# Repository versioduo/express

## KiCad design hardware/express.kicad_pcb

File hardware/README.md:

# express
🎚️ MIDI Expression Controller

## Schematic
[PDF](express.pdf)

## Bill Of Materials
[Interactive BOM](https://html-preview.github.io/?url=https://github.com/versioduo/express/main/hardware/express-bom.html)

# Copying
Anyone can use this public domain work without having to seek authorisation, no one can ever own it.

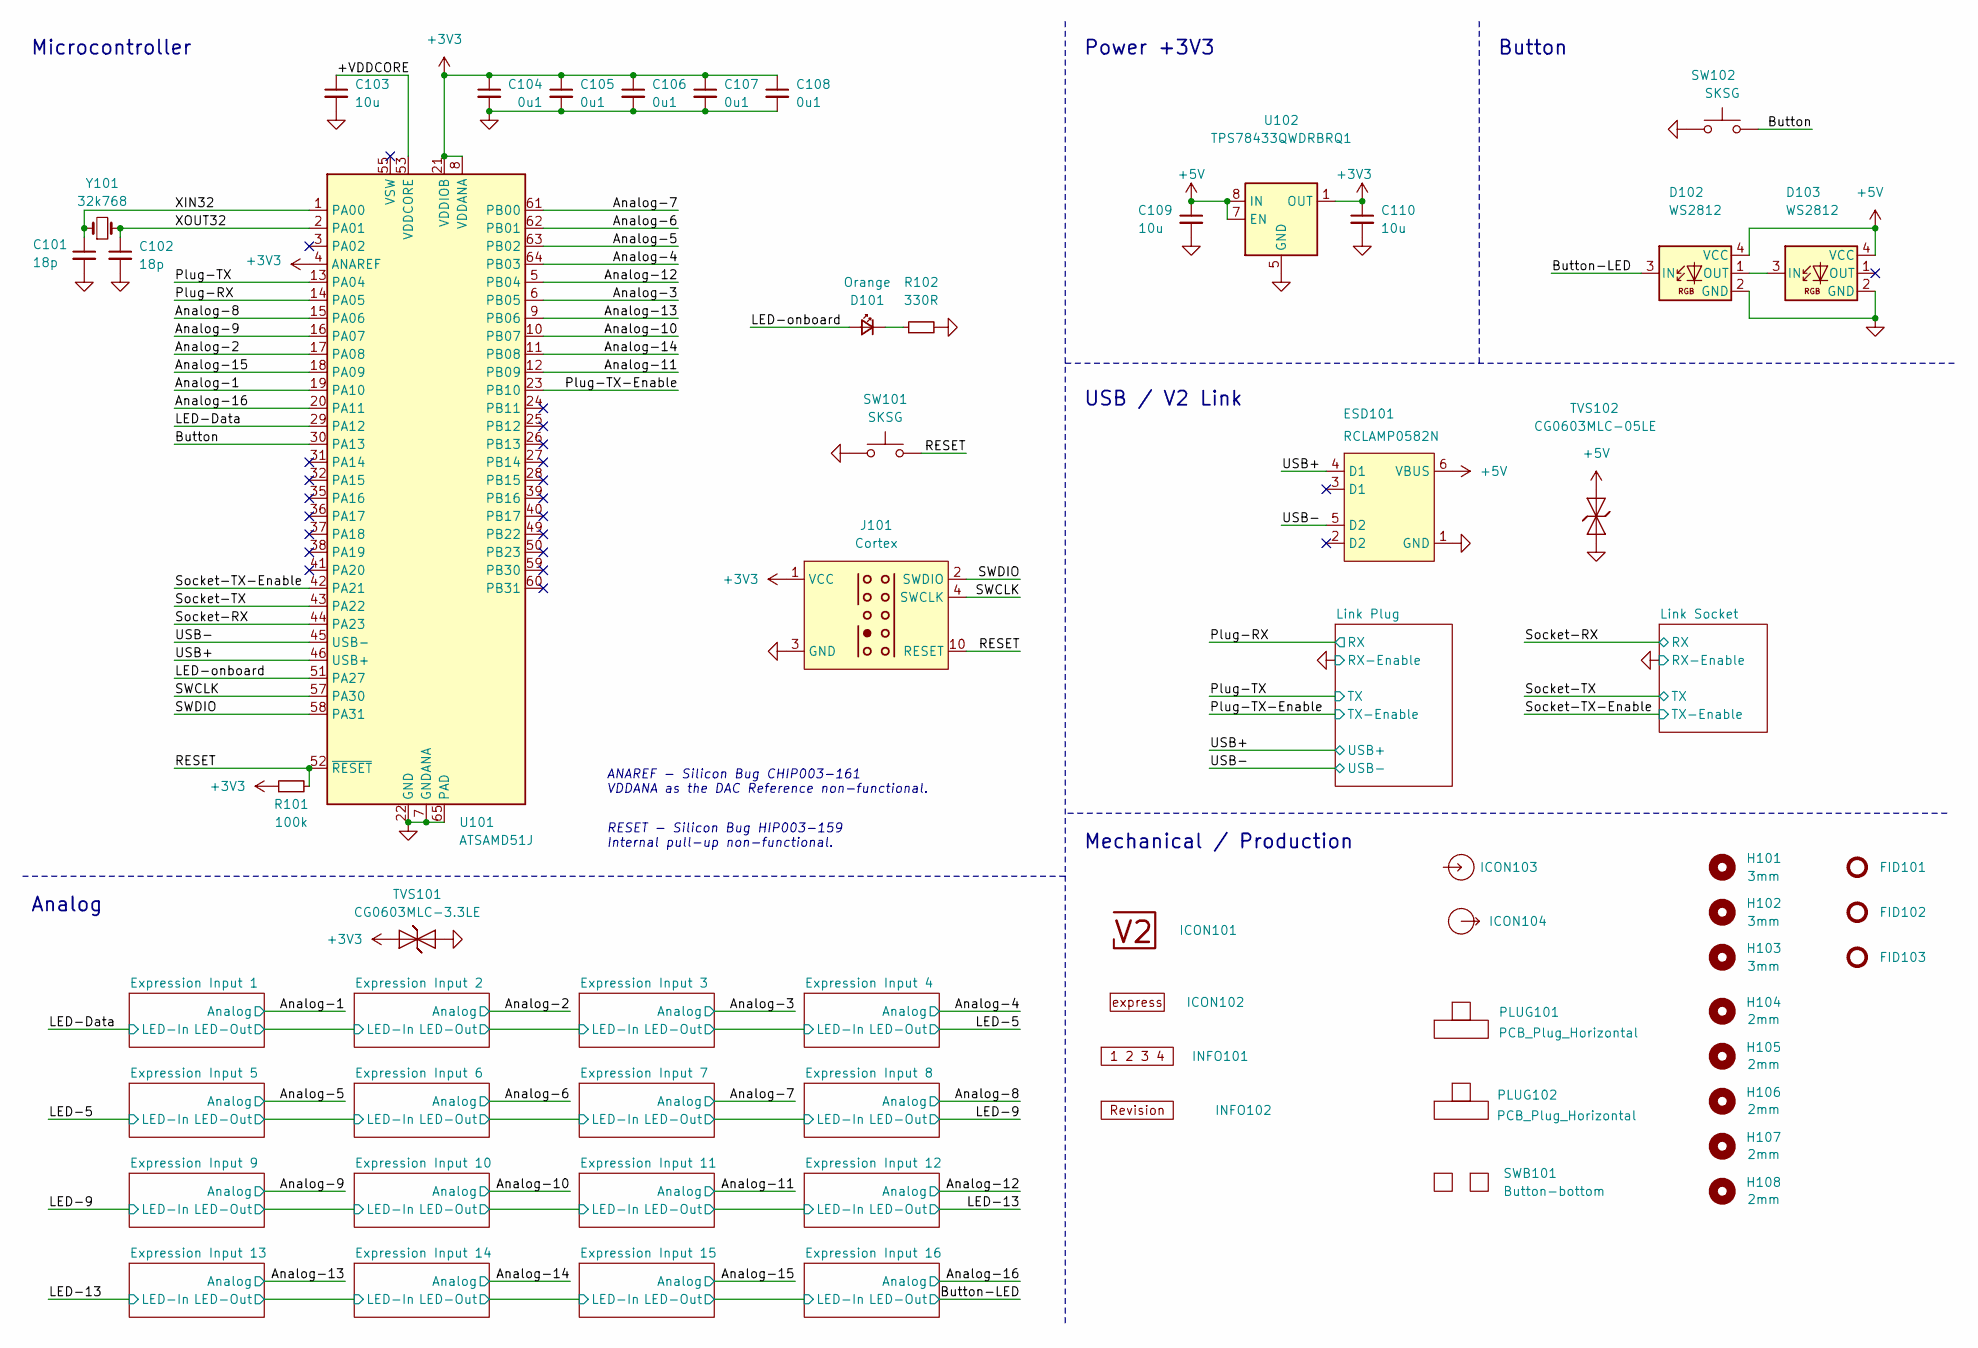
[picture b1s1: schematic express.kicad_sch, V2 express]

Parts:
C101, C102: 18p; C_0603; Rating 50V; Mouser 810-CGA3E2C0G1H180J
C103: 10u; C_0603; Rating 10V; Mouser 810-C1608X6S1A106M
C104, C105, C106, C107, C108: 0u1; C_0603; Rating 50V; Mouser 810-CGA3E2X7R1H104MA
C109, C110: 10u; C_0805; Rating 25V; Mouser 810-C2012X5R1E106K
D101: Orange; LED_0603; Rating 605nm; Mouser 755-SML-D12D1WT86
D102, D103: WS2812; WS2812-2020; Rating 15mA; LCSC C965555
ESD101: RCLAMP0582N; SLP1210N6; Rating 20kV; Mouser 947-RCLAMP0582N.TCT
FID101, FID102, FID103: Fiducial_Paste; Fiducial_0.5mm_Mask1mm_Paste
H101, H102, H103: 3mm; MountingHole_3mm
H104, H105, H106, H107, H108: 2mm; MountingHole_2mm
ICON101: V2-logo; Logo_Small
ICON102: Board_express; Board_express_Small
ICON103: Arrow_In
ICON104: Arrow_Out
INFO101: Layer_Numbers
INFO102: Revision
J101: Cortex
PLUG101, PLUG102: PCB_Plug_Horizontal
R101: 100k; R_0603; Rating 100mW; Mouser 71-CRCW0603100KFKEAC
R102: 330R; R_0603; Rating 100mW; Mouser 71-CRCW0603330RFKEAC
SW101, SW102: SKSG; Rating 1.6N; Mouser 688-SKSGACE010
SWB101: Button-bottom; PCB_Button-bottom
TVS101: CG0603MLC-3.3LE; D_0603; Rating 3V3; Mouser 652-CG0603MLC-3.3LE
TVS102: CG0603MLC-05LE; D_0603; Rating 5V; Mouser 652-CG0603MLC-05LE
U101: ATSAMD51J; QFN-64-1EP_9x9mm_P0.5mm_EP4.8x4.8mm_ThermalVias; Rating Cortex-M4F; Mouser 556-ATSAMD51J19AMU
U102: TPS78433QWDRBRQ1; VSON-8-1_3x3mm_P0.65_EP1.65x2.4mm; Rating 300mA; Mouser 595-TPS78433QWDRBRQ1
Y101: 32k768; Crystal_SMD_3215-2Pin_3.2x1.5mm; Rating 10ppm; Mouser 815-ABS0716632.768KT

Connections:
+3V3: C104.1, C105.1, C106.1, C107.1, C108.1, C110.1, J101.1 (VCC), R101.1, TVS101.1 (K), U101.4 (ANAREF), U101.8 (VDDANA), U101.21 (VDDIOB), U101.34 (VDDIO), U101.48 (VDDIO), U101.56 (VDDIO), U102.1 (OUT); also elsewhere on the board
+5V: C109.1, D102.4 (VCC), D103.4 (VCC), ESD101.6 (VBUS), TVS102.2 (A), U102.7 (EN), U102.8 (IN); also elsewhere on the board
/+VDDCORE: C103.1, U101.53 (VDDCORE)
/Analog-1: U101.19 (PA10); also elsewhere on the board
/Analog-2: U101.17 (PA08); also elsewhere on the board
/Analog-3: U101.6 (PB05); also elsewhere on the board
/Analog-4: U101.64 (PB03); also elsewhere on the board
/Analog-5: U101.63 (PB02); also elsewhere on the board
/Analog-6: U101.62 (PB01); also elsewhere on the board
/Analog-7: U101.61 (PB00); also elsewhere on the board
/Analog-8: U101.15 (PA06); also elsewhere on the board
/Analog-9: U101.16 (PA07); also elsewhere on the board
/Analog-10: U101.10 (PB07); also elsewhere on the board
/Analog-11: U101.12 (PB09); also elsewhere on the board
/Analog-12: U101.5 (PB04); also elsewhere on the board
/Analog-13: U101.9 (PB06); also elsewhere on the board
/Analog-14: U101.11 (PB08); also elsewhere on the board
/Analog-15: U101.18 (PA09); also elsewhere on the board
/Analog-16: U101.20 (PA11); also elsewhere on the board
/Button: SW102.2, U101.30 (PA13)
/Button-LED: D102.3 (IN); also elsewhere on the board
/LED-Data: U101.29 (PA12); also elsewhere on the board
/LED-onboard: D101.2 (A), U101.51 (PA27)
/Plug-RX: U101.14 (PA05); also elsewhere on the board
/Plug-TX: U101.13 (PA04); also elsewhere on the board
/Plug-TX-Enable: U101.23 (PB10); also elsewhere on the board
/RESET: J101.10 (RESET), R101.2, SW101.2, U101.52 (~RESET)
/SWCLK: J101.4 (SWCLK), U101.57 (PA30)
/SWDIO: J101.2 (SWDIO), U101.58 (PA31)
/Socket-RX: U101.44 (PA23); also elsewhere on the board
/Socket-TX: U101.43 (PA22); also elsewhere on the board
/Socket-TX-Enable: U101.42 (PA21); also elsewhere on the board
/USB+: ESD101.4 (D1), U101.46 (USB+); also elsewhere on the board
/USB-: ESD101.5 (D2), U101.45 (USB-); also elsewhere on the board
/XIN32: C101.1, U101.1 (PA00), Y101.1
/XOUT32: C102.1, U101.2 (PA01), Y101.2
GND: C101.2, C102.2, C103.2, C104.2, C105.2, C106.2, C107.2, C108.2, C109.2, C110.2, D102.2 (GND), D103.2 (GND), ESD101.1 (GND), J101.3 (GND), J101.5 (GND), R102.2, SW101.1, SW102.1, TVS101.2 (A), TVS102.1 (K), U101.7 (GNDANA), U101.22 (GND), U101.33 (GND), U101.47 (GND), U101.54 (GND), U101.65 (PAD), U102.5 (GND), U102.9 (GND); also elsewhere on the board
unnamed: D101.1 (K), R102.1
unnamed: D102.1 (OUT), D103.3 (IN)

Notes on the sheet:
ANAREF - ﻿Silicon Bug CHIP003-161 VDDANA as the DAC Reference non-functional.
Analog
RESET - ﻿Silicon Bug HIP003-159 Internal pull-up non-functional.
Button
Power +3V3
Mechanical / Production
Microcontroller
USB / V2 Link

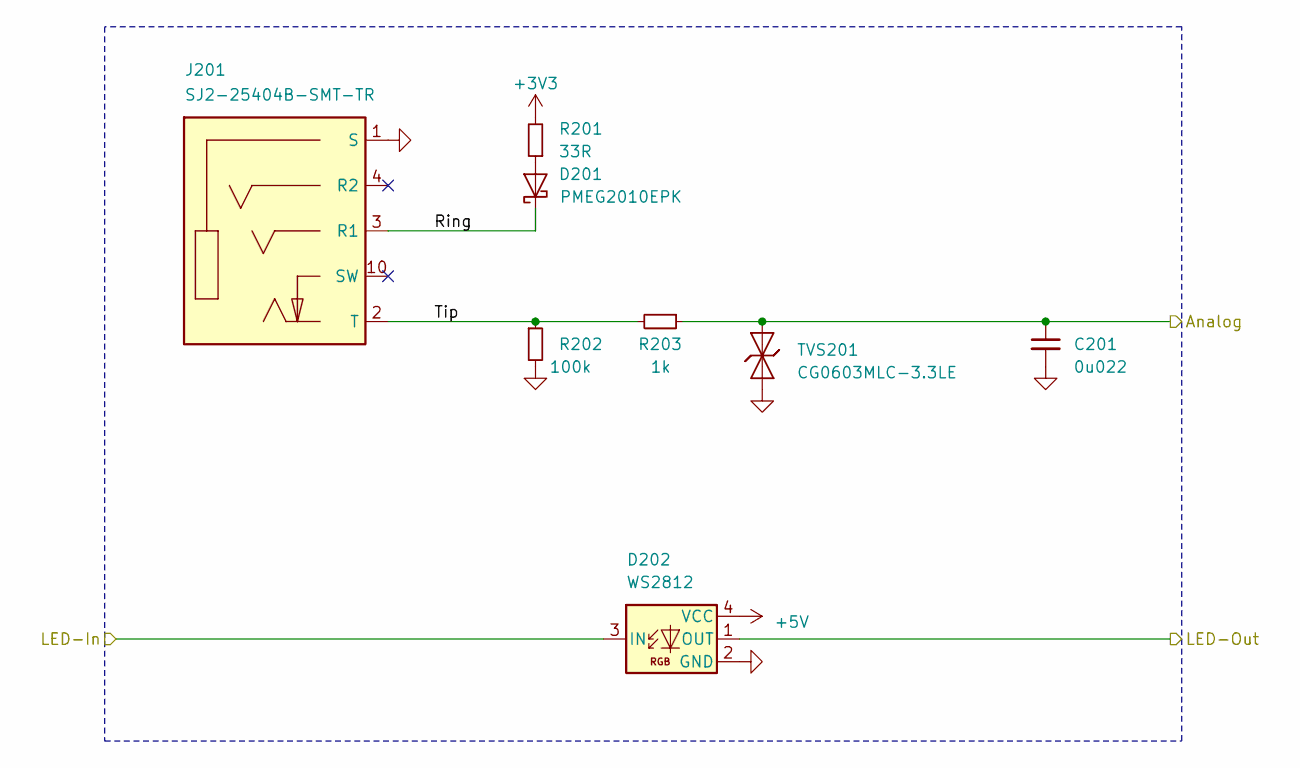
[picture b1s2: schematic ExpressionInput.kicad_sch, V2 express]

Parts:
C201: 0u022; C_0603; Rating 50V; Mouser 603-CC603KPX7R9BB223
D201: PMEG2010EPK; D_SOD-1608; Rating 20V; Mouser 771-PMEG2010EPK
D202: WS2812; WS2812-2020; Rating 15mA; LCSC C965555
J201: SJ2-25404B-SMT-TR; CUI_SJ2-25404B-SMT-TR; Rating 2.5mm; Mouser 490-SJ2-25404BSMT-TR
R201: 33R; R_0603; Rating 330mW; Mouser 71-CRCW060333R0FKEAH
R202: 100k; R_0603; Rating 100mW; Mouser 71-CRCW0603100KFKEAC
R203: 1k; R_0603; Rating 330mW; Mouser 71-CRCW06031K00FKEAH
TVS201: CG0603MLC-3.3LE; D_0603; Rating 3V3; Mouser 652-CG0603MLC-3.3LE

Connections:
+3V3: R201.2; also elsewhere on the board
+5V: D202.4 (VCC); also elsewhere on the board
/Analog-1: C201.1, R203.1, TVS201.2 (A); also elsewhere on the board
/Expression Input 1/LED-Out: D202.1 (OUT); also elsewhere on the board
/Expression Input 1/Ring: D201.1 (K), J201.3 (R1)
/Expression Input 1/Tip: J201.2 (T), R202.1, R203.2
/LED-Data: D202.3 (IN); also elsewhere on the board
GND: C201.2, D202.2 (GND), J201.1 (S), R202.2, TVS201.1 (K); also elsewhere on the board
unnamed: D201.2 (A), R201.1

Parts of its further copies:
C301, C401, C501, C601, C701, C801, C901, C1001, C1101, C1201, C1301, C1401, C1501, C1601, C1701: 0u022; C_0603; Rating 50V; Mouser 603-CC603KPX7R9BB223
D301, D401, D501, D601, D701, D801, D901, D1001, D1101, D1201, D1301, D1401, D1501, D1601, D1701: PMEG2010EPK; D_SOD-1608; Rating 20V; Mouser 771-PMEG2010EPK
D302, D402, D502, D602, D702, D802, D902, D1002, D1102, D1202, D1302, D1402, D1502, D1602, D1702: WS2812; WS2812-2020; Rating 15mA; LCSC C965555
J301, J401, J501, J601, J701, J801, J901, J1001, J1101, J1201, J1301, J1401, J1501, J1601, J1701: SJ2-25404B-SMT-TR; CUI_SJ2-25404B-SMT-TR; Rating 2.5mm; Mouser 490-SJ2-25404BSMT-TR
R301, R401, R501, R601, R701, R801, R901, R1001, R1101, R1201, R1301, R1401, R1501, R1601, R1701: 33R; R_0603; Rating 330mW; Mouser 71-CRCW060333R0FKEAH
R302, R402, R502, R602, R702, R802, R902, R1002, R1102, R1202, R1302, R1402, R1502, R1602, R1702: 100k; R_0603; Rating 100mW; Mouser 71-CRCW0603100KFKEAC
R303, R403, R503, R603, R703, R803, R903, R1003, R1103, R1203, R1303, R1403, R1503, R1603, R1703: 1k; R_0603; Rating 330mW; Mouser 71-CRCW06031K00FKEAH
TVS301, TVS401, TVS501, TVS601, TVS701, TVS801, TVS901, TVS1001, TVS1101, TVS1201, TVS1301, TVS1401, TVS1501, TVS1601, TVS1701: CG0603MLC-3.3LE; D_0603; Rating 3V3; Mouser 652-CG0603MLC-3.3LE

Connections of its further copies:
+3V3: R301.2, R401.2, R501.2, R601.2, R701.2, R801.2, R901.2, R1001.2, R1101.2, R1201.2, R1301.2, R1401.2, R1501.2, R1601.2, R1701.2; also elsewhere on the board
+5V: D302.4 (VCC), D402.4 (VCC), D502.4 (VCC), D602.4 (VCC), D702.4 (VCC), D802.4 (VCC), D902.4 (VCC), D1002.4 (VCC), D1102.4 (VCC), D1202.4 (VCC), D1302.4 (VCC), D1402.4 (VCC), D1502.4 (VCC), D1602.4 (VCC), D1702.4 (VCC); also elsewhere on the board
/Analog-2: C301.1, R303.1, TVS301.2 (A); also elsewhere on the board
/Analog-3: C401.1, R403.1, TVS401.2 (A); also elsewhere on the board
/Analog-4: C501.1, R503.1, TVS501.2 (A); also elsewhere on the board
/Analog-5: C601.1, R603.1, TVS601.2 (A); also elsewhere on the board
/Analog-6: C701.1, R703.1, TVS701.2 (A); also elsewhere on the board
/Analog-7: C801.1, R803.1, TVS801.2 (A); also elsewhere on the board
/Analog-8: C901.1, R903.1, TVS901.2 (A); also elsewhere on the board
/Analog-9: C1001.1, R1003.1, TVS1001.2 (A); also elsewhere on the board
/Analog-10: C1101.1, R1103.1, TVS1101.2 (A); also elsewhere on the board
/Analog-11: C1201.1, R1203.1, TVS1201.2 (A); also elsewhere on the board
/Analog-12: C1301.1, R1303.1, TVS1301.2 (A); also elsewhere on the board
/Analog-13: C1401.1, R1403.1, TVS1401.2 (A); also elsewhere on the board
/Analog-14: C1501.1, R1503.1, TVS1501.2 (A); also elsewhere on the board
/Analog-15: C1601.1, R1603.1, TVS1601.2 (A); also elsewhere on the board
/Analog-16: C1701.1, R1703.1, TVS1701.2 (A); also elsewhere on the board
/Button-LED: D1702.1 (OUT); also elsewhere on the board
/Expression Input 1/LED-Out: D302.3 (IN); also elsewhere on the board
/Expression Input 2/LED-Out: D302.1 (OUT), D402.3 (IN)
/Expression Input 2/Ring: D301.1 (K), J301.3 (R1)
/Expression Input 2/Tip: J301.2 (T), R302.1, R303.2
/Expression Input 3/LED-Out: D402.1 (OUT), D502.3 (IN)
/Expression Input 3/Ring: D401.1 (K), J401.3 (R1)
/Expression Input 3/Tip: J401.2 (T), R402.1, R403.2
/Expression Input 4/Ring: D501.1 (K), J501.3 (R1)
/Expression Input 4/Tip: J501.2 (T), R502.1, R503.2
/Expression Input 5/LED-Out: D602.1 (OUT), D702.3 (IN)
/Expression Input 5/Ring: D601.1 (K), J601.3 (R1)
/Expression Input 5/Tip: J601.2 (T), R602.1, R603.2
/Expression Input 6/LED-Out: D702.1 (OUT), D802.3 (IN)
/Expression Input 6/Ring: D701.1 (K), J701.3 (R1)
/Expression Input 6/Tip: J701.2 (T), R702.1, R703.2
/Expression Input 7/LED-Out: D802.1 (OUT), D902.3 (IN)
/Expression Input 7/Ring: D801.1 (K), J801.3 (R1)
/Expression Input 7/Tip: J801.2 (T), R802.1, R803.2
/Expression Input 8/Ring: D901.1 (K), J901.3 (R1)
/Expression Input 8/Tip: J901.2 (T), R902.1, R903.2
/Expression Input 9/Ring: D1001.1 (K), J1001.3 (R1)
/Expression Input 9/Tip: J1001.2 (T), R1002.1, R1003.2
/Expression Input 10/LED-In: D1002.1 (OUT), D1102.3 (IN)
/Expression Input 10/LED-Out: D1102.1 (OUT), D1202.3 (IN)
/Expression Input 10/Ring: D1101.1 (K), J1101.3 (R1)
/Expression Input 10/Tip: J1101.2 (T), R1102.1, R1103.2
/Expression Input 11/LED-Out: D1202.1 (OUT), D1302.3 (IN)
/Expression Input 11/Ring: D1201.1 (K), J1201.3 (R1)
/Expression Input 11/Tip: J1201.2 (T), R1202.1, R1203.2
/Expression Input 12/Ring: D1301.1 (K), J1301.3 (R1)
/Expression Input 12/Tip: J1301.2 (T), R1302.1, R1303.2
/Expression Input 13/LED-Out: D1402.1 (OUT), D1502.3 (IN)
/Expression Input 13/Ring: D1401.1 (K), J1401.3 (R1)
/Expression Input 13/Tip: J1401.2 (T), R1402.1, R1403.2
/Expression Input 14/LED-Out: D1502.1 (OUT), D1602.3 (IN)
/Expression Input 14/Ring: D1501.1 (K), J1501.3 (R1)
/Expression Input 14/Tip: J1501.2 (T), R1502.1, R1503.2
/Expression Input 15/LED-Out: D1602.1 (OUT), D1702.3 (IN)
/Expression Input 15/Ring: D1601.1 (K), J1601.3 (R1)
/Expression Input 15/Tip: J1601.2 (T), R1602.1, R1603.2
/Expression Input 16/Ring: D1701.1 (K), J1701.3 (R1)
/Expression Input 16/Tip: J1701.2 (T), R1702.1, R1703.2
/LED-5: D502.1 (OUT), D602.3 (IN)
/LED-9: D902.1 (OUT), D1002.3 (IN)
/LED-13: D1302.1 (OUT), D1402.3 (IN)
GND: C301.2, C401.2, C501.2, C601.2, C701.2, C801.2, C901.2, C1001.2, C1101.2, C1201.2, C1301.2, C1401.2, C1501.2, C1601.2, C1701.2, D302.2 (GND), D402.2 (GND), D502.2 (GND), D602.2 (GND), D702.2 (GND), D802.2 (GND), D902.2 (GND), D1002.2 (GND), D1102.2 (GND), D1202.2 (GND), D1302.2 (GND), D1402.2 (GND), D1502.2 (GND), D1602.2 (GND), D1702.2 (GND), J301.1 (S), J401.1 (S), J501.1 (S), J601.1 (S), J701.1 (S), J801.1 (S), J901.1 (S), J1001.1 (S), J1101.1 (S), J1201.1 (S), J1301.1 (S), J1401.1 (S), J1501.1 (S), J1601.1 (S), J1701.1 (S), R302.2, R402.2, R502.2, R602.2, R702.2, R802.2, R902.2, R1002.2, R1102.2, R1202.2, R1302.2, R1402.2, R1502.2, R1602.2, R1702.2, TVS301.1 (K), TVS401.1 (K), TVS501.1 (K), TVS601.1 (K), TVS701.1 (K), TVS801.1 (K), TVS901.1 (K), TVS1001.1 (K), TVS1101.1 (K), TVS1201.1 (K), TVS1301.1 (K), TVS1401.1 (K), TVS1501.1 (K), TVS1601.1 (K), TVS1701.1 (K); also elsewhere on the board
unnamed: D301.2 (A), R301.1
unnamed: D401.2 (A), R401.1
unnamed: D501.2 (A), R501.1
unnamed: D601.2 (A), R601.1
unnamed: D701.2 (A), R701.1
unnamed: D801.2 (A), R801.1
unnamed: D901.2 (A), R901.1
unnamed: D1001.2 (A), R1001.1
unnamed: D1101.2 (A), R1101.1
unnamed: D1201.2 (A), R1201.1
unnamed: D1301.2 (A), R1301.1
unnamed: D1401.2 (A), R1401.1
unnamed: D1501.2 (A), R1501.1
unnamed: D1601.2 (A), R1601.1
unnamed: D1701.2 (A), R1701.1

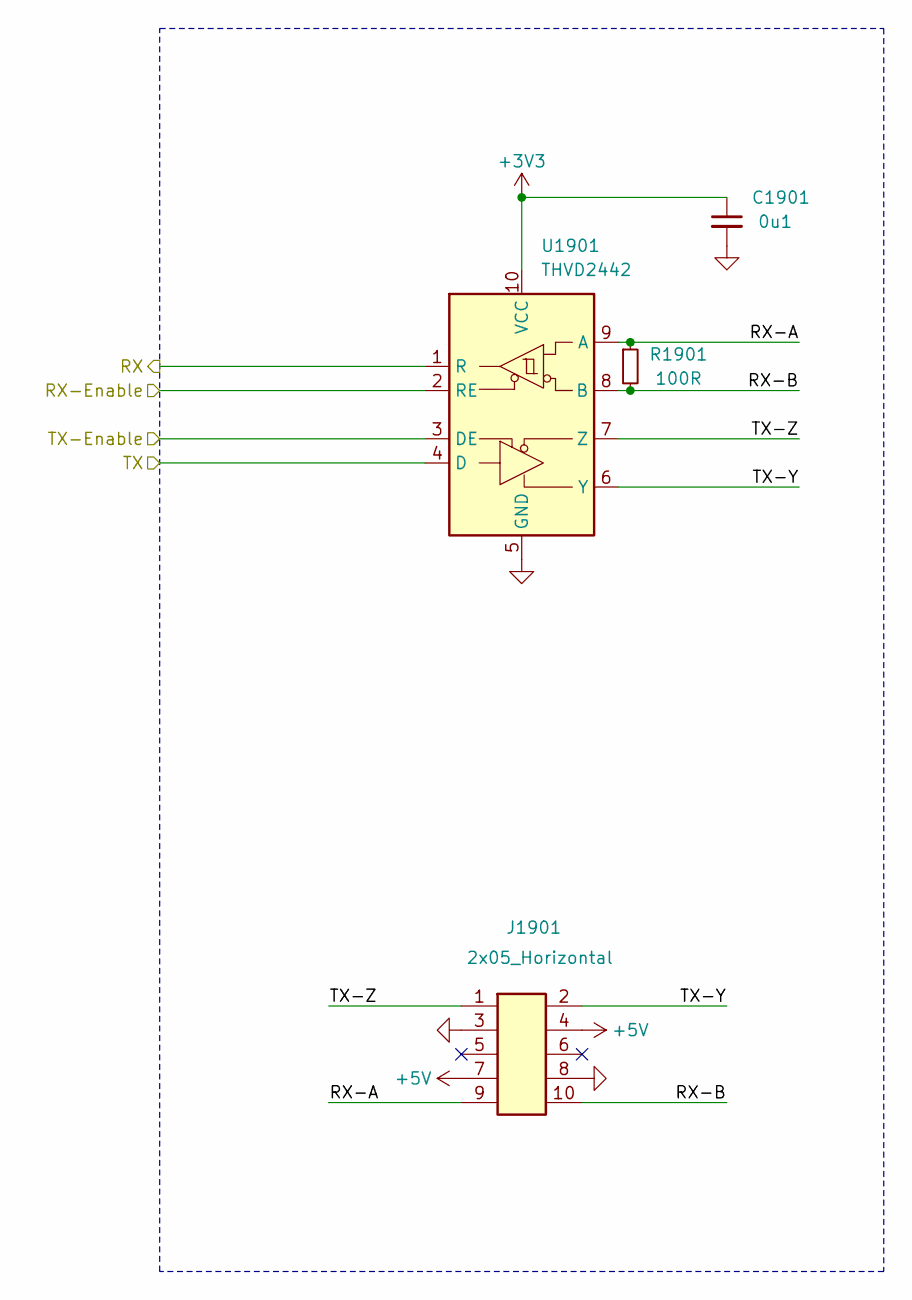
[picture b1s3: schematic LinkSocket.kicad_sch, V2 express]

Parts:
C1901: 0u1; C_0603; Rating 50V; Mouser 810-CGA3E2X7R1H104MA
J1901: 2x05_Horizontal; PinHeader_2x05_P1.27mm_Horizontal; Rating 1A; Mouser 649-200211120001T4LF
R1901: 100R; R_0603; Rating 330mW; Mouser 71-CRCW0603100RFKEAH
U1901: THVD2442; VSON-10-4-1EP_3x3mm_P0.5mm_EP1.65x2.4mm_ThermalVias; Rating 20Mbps; Mouser 595-THVD2442DRCR

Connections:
+3V3: C1901.1, U1901.10 (VCC); also elsewhere on the board
+5V: J1901.4, J1901.7; also elsewhere on the board
/Link Socket/RX-A: J1901.9, R1901.1, U1901.9 (A)
/Link Socket/RX-B: J1901.10, R1901.2, U1901.8 (B)
/Link Socket/TX-Y: J1901.2, U1901.6 (Y)
/Link Socket/TX-Z: J1901.1, U1901.7 (Z)
/Socket-RX: U1901.1 (R); also elsewhere on the board
/Socket-TX: U1901.4 (D); also elsewhere on the board
/Socket-TX-Enable: U1901.3 (DE); also elsewhere on the board
GND: C1901.2, J1901.3, J1901.8, U1901.2 (RE), U1901.5 (GND), U1901.11 (GND); also elsewhere on the board

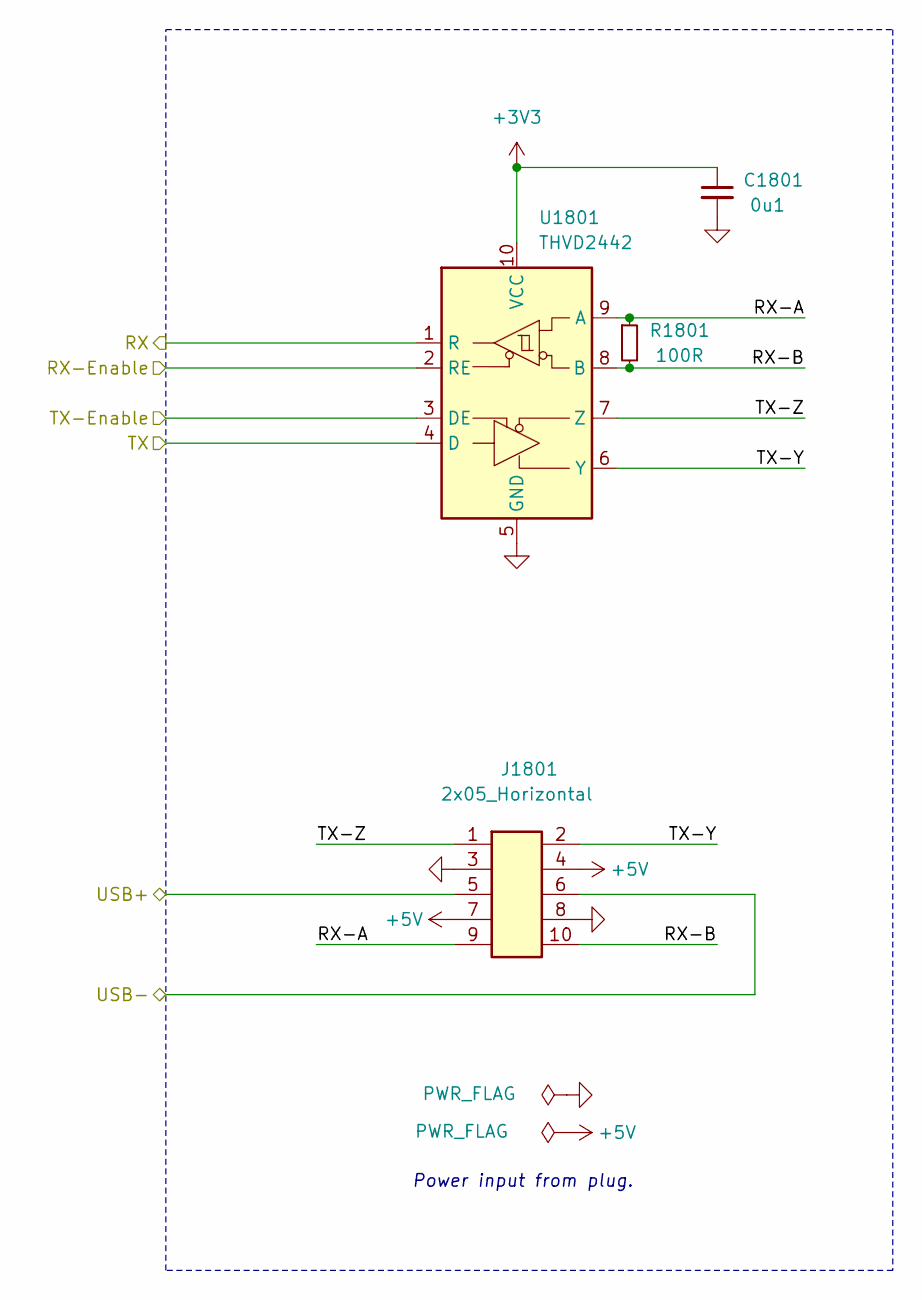
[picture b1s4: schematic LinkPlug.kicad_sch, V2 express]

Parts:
C1801: 0u1; C_0603; Rating 50V; Mouser 810-CGA3E2X7R1H104MA
J1801: 2x05_Horizontal; PinHeader_2x05_P1.27mm_Horizontal; Rating 1A; Mouser 649-200211120001T4LF
R1801: 100R; R_0603; Rating 330mW; Mouser 71-CRCW0603100RFKEAH
U1801: THVD2442; VSON-10-4-1EP_3x3mm_P0.5mm_EP1.65x2.4mm_ThermalVias; Rating 20Mbps; Mouser 595-THVD2442DRCR

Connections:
+3V3: C1801.1, U1801.10 (VCC); also elsewhere on the board
+5V: J1801.4, J1801.7; also elsewhere on the board
/Link Plug/RX-A: J1801.9, R1801.1, U1801.9 (A)
/Link Plug/RX-B: J1801.10, R1801.2, U1801.8 (B)
/Link Plug/TX-Y: J1801.2, U1801.6 (Y)
/Link Plug/TX-Z: J1801.1, U1801.7 (Z)
/Plug-RX: U1801.1 (R); also elsewhere on the board
/Plug-TX: U1801.4 (D); also elsewhere on the board
/Plug-TX-Enable: U1801.3 (DE); also elsewhere on the board
/USB+: J1801.5; also elsewhere on the board
/USB-: J1801.6; also elsewhere on the board
GND: C1801.2, J1801.3, J1801.8, U1801.2 (RE), U1801.5 (GND), U1801.11 (GND); also elsewhere on the board

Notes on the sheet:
Power input from plug.

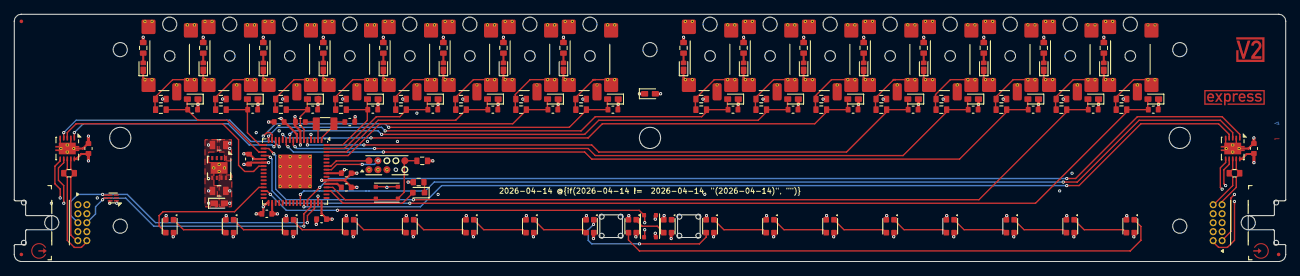
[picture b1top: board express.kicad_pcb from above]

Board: 4 copper layers, 180.0 x 35.0 mm, 180 parts (0 on the bottom side), 110 nets.

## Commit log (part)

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2021-08-06 Import
2024-01-21 ArduinoJson 7
2026-02-13 Replace Order_Number
2026-02-15 Update Library
2026-03-14 Update ESD suppressor
2026-03-30 Replace diode
2026-05-11 Good Bye Imperial
2026-06-21 Update MIDI API
2026-06-23 Update V2Link API
